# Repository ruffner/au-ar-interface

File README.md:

# au-ar-interface
machine vision and hdmi interface for alchitry labs au artix 7 fpga

## layer stackup
I use pcbway and this is the layer configuration from them that this board is based on. 

## hdmi impedance calcluation and design considerations
Saturn PCB Toolkit was used to calculate the necessary trace widths and spacing to achieve the 100 ohm differential impedance target of the HDMI specification.

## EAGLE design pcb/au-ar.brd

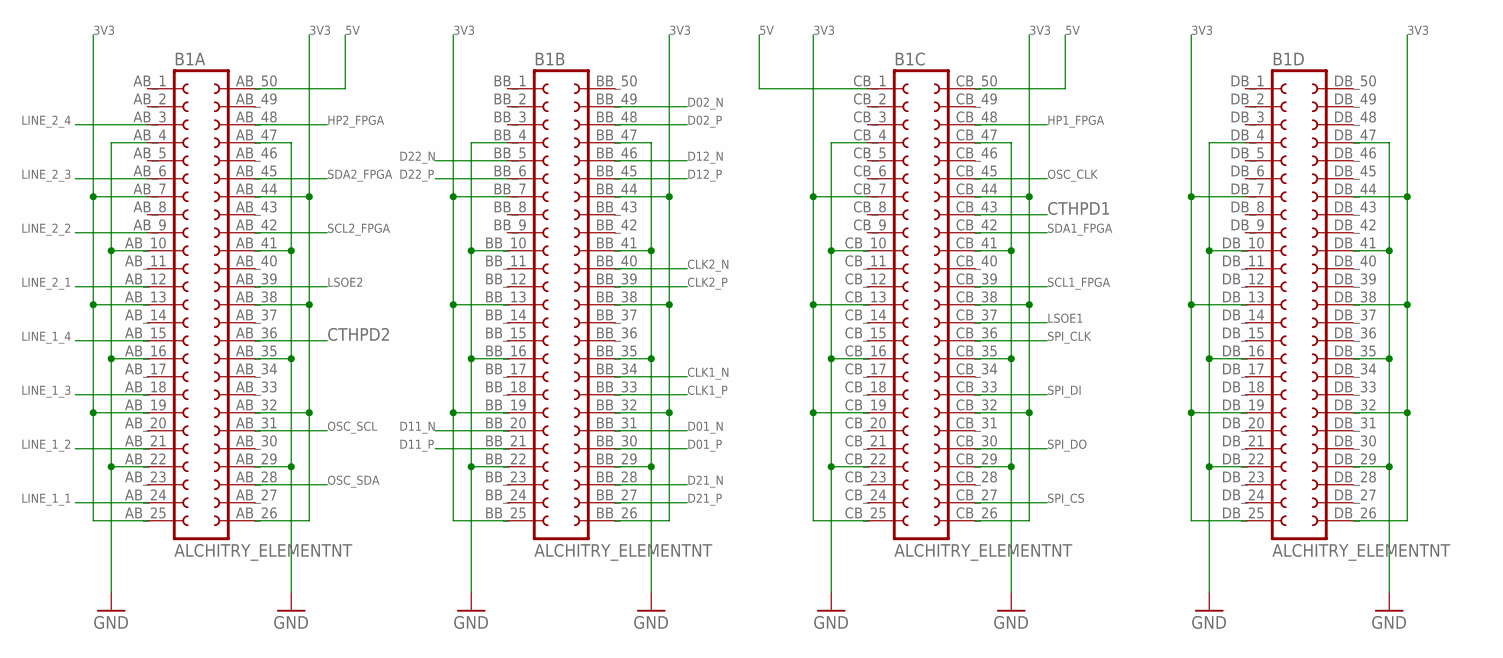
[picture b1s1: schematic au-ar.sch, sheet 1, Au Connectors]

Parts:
B1: ALCHITRY_ELEMENTNT; ELEMENT_NO_TOP

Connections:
3V3: B1.AB_7 (7), B1.AB_13 (13), B1.AB_19 (19), B1.AB_25 (25), B1.AB_26 (26), B1.AB_32 (32), B1.AB_38 (38), B1.AB_44 (44), B1.BB_7 (7), B1.BB_13 (13), B1.BB_19 (19), B1.BB_25 (25), B1.BB_26 (26), B1.BB_32 (32), B1.BB_38 (38), B1.BB_44 (44), B1.CB_7 (7), B1.CB_13 (13), B1.CB_19 (19), B1.CB_25 (25), B1.CB_26 (26), B1.CB_32 (32), B1.CB_38 (38), B1.CB_44 (44), B1.DB_7 (7), B1.DB_13 (13), B1.DB_19 (19), B1.DB_25 (25), B1.DB_26 (26), B1.DB_32 (32), B1.DB_38 (38), B1.DB_44 (44); also elsewhere on the board
5V: B1.AB_50 (50), B1.CB_1 (1), B1.CB_50 (50); also elsewhere on the board
CLK1_N: B1.BB_34 (34); also elsewhere on the board
CLK1_P: B1.BB_33 (33); also elsewhere on the board
CLK2_N: B1.BB_40 (40); also elsewhere on the board
CLK2_P: B1.BB_39 (39); also elsewhere on the board
CTHPD1: B1.CB_43 (43); also elsewhere on the board
CTHPD2: B1.AB_36 (36); also elsewhere on the board
D01_N: B1.BB_31 (31); also elsewhere on the board
D01_P: B1.BB_30 (30); also elsewhere on the board
D02_N: B1.BB_49 (49); also elsewhere on the board
D02_P: B1.BB_48 (48); also elsewhere on the board
D11_N: B1.BB_20 (20); also elsewhere on the board
D11_P: B1.BB_21 (21); also elsewhere on the board
D12_N: B1.BB_46 (46); also elsewhere on the board
D12_P: B1.BB_45 (45); also elsewhere on the board
D21_N: B1.BB_28 (28); also elsewhere on the board
D21_P: B1.BB_27 (27); also elsewhere on the board
D22_N: B1.BB_5 (5); also elsewhere on the board
D22_P: B1.BB_6 (6); also elsewhere on the board
GND: B1.AB_4 (4), B1.AB_10 (10), B1.AB_16 (16), B1.AB_22 (22), B1.AB_29 (29), B1.AB_35 (35), B1.AB_41 (41), B1.AB_47 (47), B1.BB_4 (4), B1.BB_10 (10), B1.BB_16 (16), B1.BB_22 (22), B1.BB_29 (29), B1.BB_35 (35), B1.BB_41 (41), B1.BB_47 (47), B1.CB_4 (4), B1.CB_10 (10), B1.CB_16 (16), B1.CB_22 (22), B1.CB_29 (29), B1.CB_35 (35), B1.CB_41 (41), B1.CB_47 (47), B1.DB_4 (4), B1.DB_10 (10), B1.DB_16 (16), B1.DB_22 (22), B1.DB_29 (29), B1.DB_35 (35), B1.DB_41 (41), B1.DB_47 (47); also elsewhere on the board
HP1_FPGA: B1.CB_48 (48); also elsewhere on the board
HP2_FPGA: B1.AB_48 (48); also elsewhere on the board
LINE_1_1: B1.AB_24 (24); also elsewhere on the board
LINE_1_2: B1.AB_21 (21); also elsewhere on the board
LINE_1_3: B1.AB_18 (18); also elsewhere on the board
LINE_1_4: B1.AB_15 (15); also elsewhere on the board
LINE_2_1: B1.AB_12 (12); also elsewhere on the board
LINE_2_2: B1.AB_9 (9); also elsewhere on the board
LINE_2_3: B1.AB_6 (6); also elsewhere on the board
LINE_2_4: B1.AB_3 (3); also elsewhere on the board
LSOE1: B1.CB_37 (37); also elsewhere on the board
LSOE2: B1.AB_39 (39); also elsewhere on the board
OSC_CLK: B1.CB_45 (45); also elsewhere on the board
OSC_SCL: B1.AB_31 (31); also elsewhere on the board
OSC_SDA: B1.AB_28 (28); also elsewhere on the board
SCL1_FPGA: B1.CB_39 (39); also elsewhere on the board
SCL2_FPGA: B1.AB_42 (42); also elsewhere on the board
SDA1_FPGA: B1.CB_42 (42); also elsewhere on the board
SDA2_FPGA: B1.AB_45 (45); also elsewhere on the board
SPI_CLK: B1.CB_36 (36); also elsewhere on the board
SPI_CS: B1.CB_27 (27); also elsewhere on the board
SPI_DI: B1.CB_33 (33); also elsewhere on the board
SPI_DO: B1.CB_30 (30); also elsewhere on the board

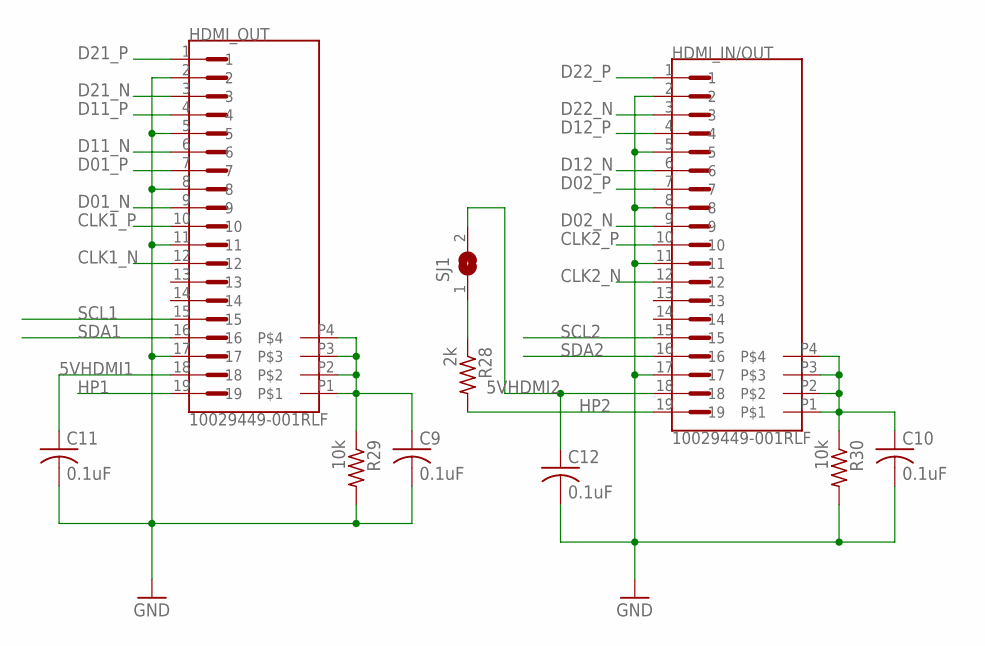
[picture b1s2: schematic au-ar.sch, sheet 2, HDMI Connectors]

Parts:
C9, C10, C11, C12: 0.1uF; C0603
HDMI_IN/OUT: 10029449-001RLF; FCI_10029449-001RLF
HDMI_OUT: 10029449-001RLF; FCI_10029449-001RLF
R28: 2k; R0603
R29, R30: 10k; R0603
SJ1: SJ

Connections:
5VHDMI1: C11.1, HDMI_OUT.18; also elsewhere on the board
5VHDMI2: C12.1, HDMI_IN/OUT.18, SJ1.2; also elsewhere on the board
CLK1_N: HDMI_OUT.12; also elsewhere on the board
CLK1_P: HDMI_OUT.10; also elsewhere on the board
CLK2_N: HDMI_IN/OUT.12; also elsewhere on the board
CLK2_P: HDMI_IN/OUT.10; also elsewhere on the board
D01_N: HDMI_OUT.9; also elsewhere on the board
D01_P: HDMI_OUT.7; also elsewhere on the board
D02_N: HDMI_IN/OUT.9; also elsewhere on the board
D02_P: HDMI_IN/OUT.7; also elsewhere on the board
D11_N: HDMI_OUT.6; also elsewhere on the board
D11_P: HDMI_OUT.4; also elsewhere on the board
D12_N: HDMI_IN/OUT.6; also elsewhere on the board
D12_P: HDMI_IN/OUT.4; also elsewhere on the board
D21_N: HDMI_OUT.3; also elsewhere on the board
D21_P: HDMI_OUT.1; also elsewhere on the board
D22_N: HDMI_IN/OUT.3; also elsewhere on the board
D22_P: HDMI_IN/OUT.1; also elsewhere on the board
GND: C9.2, C10.2, C11.2, C12.2, HDMI_IN/OUT.2, HDMI_IN/OUT.5, HDMI_IN/OUT.8, HDMI_IN/OUT.11, HDMI_IN/OUT.17, HDMI_OUT.2, HDMI_OUT.5, HDMI_OUT.8, HDMI_OUT.11, HDMI_OUT.17, R29.2, R30.2; also elsewhere on the board
HP1: HDMI_OUT.19; also elsewhere on the board
HP2: HDMI_IN/OUT.19, R28.2; also elsewhere on the board
unnamed: R28.1, SJ1.1
unnamed: C9.1, HDMI_OUT.P1, HDMI_OUT.P2, HDMI_OUT.P3, HDMI_OUT.P4, R29.1
unnamed: C10.1, HDMI_IN/OUT.P1, HDMI_IN/OUT.P2, HDMI_IN/OUT.P3, HDMI_IN/OUT.P4, R30.1
SCL1: HDMI_OUT.15; also elsewhere on the board
SCL2: HDMI_IN/OUT.15; also elsewhere on the board
SDA1: HDMI_OUT.16; also elsewhere on the board
SDA2: HDMI_IN/OUT.16; also elsewhere on the board

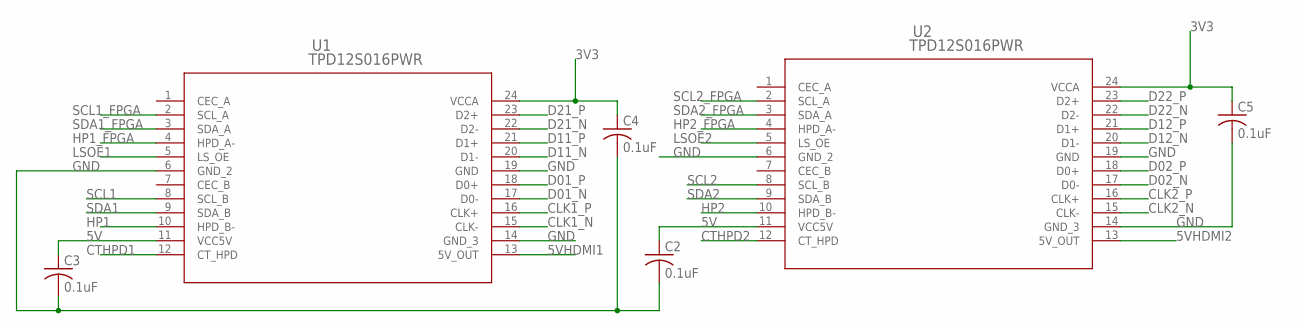
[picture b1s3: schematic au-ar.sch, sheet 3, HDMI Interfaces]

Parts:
C2, C3, C4, C5: 0.1uF; C0603
U1, U2: TPD12S016PWR; PW24

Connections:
3V3: C4.1, C5.1, U1.24 (VCCA), U2.24 (VCCA); also elsewhere on the board
5V: C2.1, C3.1, U1.11 (VCC5V), U2.11 (VCC5V); also elsewhere on the board
5VHDMI1: U1.13 (5V_OUT); also elsewhere on the board
5VHDMI2: U2.13 (5V_OUT); also elsewhere on the board
CLK1_N: U1.15 (CLK-); also elsewhere on the board
CLK1_P: U1.16 (CLK+); also elsewhere on the board
CLK2_N: U2.15 (CLK-); also elsewhere on the board
CLK2_P: U2.16 (CLK+); also elsewhere on the board
CTHPD1: U1.12 (CT_HPD); also elsewhere on the board
CTHPD2: U2.12 (CT_HPD); also elsewhere on the board
D01_N: U1.17 (D0-); also elsewhere on the board
D01_P: U1.18 (D0+); also elsewhere on the board
D02_N: U2.17 (D0-); also elsewhere on the board
D02_P: U2.18 (D0+); also elsewhere on the board
D11_N: U1.20 (D1-); also elsewhere on the board
D11_P: U1.21 (D1+); also elsewhere on the board
D12_N: U2.20 (D1-); also elsewhere on the board
D12_P: U2.21 (D1+); also elsewhere on the board
D21_N: U1.22 (D2-); also elsewhere on the board
D21_P: U1.23 (D2+); also elsewhere on the board
D22_N: U2.22 (D2-); also elsewhere on the board
D22_P: U2.23 (D2+); also elsewhere on the board
GND: C2.2, C3.2, C4.2, C5.2, U1.6 (GND_2), U1.14 (GND_3), U1.19 (GND), U2.6 (GND_2), U2.14 (GND_3), U2.19 (GND); also elsewhere on the board
HP1: U1.10 (HPD_B-); also elsewhere on the board
HP1_FPGA: U1.4 (HPD_A-); also elsewhere on the board
HP2: U2.10 (HPD_B-); also elsewhere on the board
HP2_FPGA: U2.4 (HPD_A-); also elsewhere on the board
LSOE1: U1.5 (LS_OE); also elsewhere on the board
LSOE2: U2.5 (LS_OE); also elsewhere on the board
SCL1: U1.8 (SCL_B); also elsewhere on the board
SCL1_FPGA: U1.2 (SCL_A); also elsewhere on the board
SCL2: U2.8 (SCL_B); also elsewhere on the board
SCL2_FPGA: U2.2 (SCL_A); also elsewhere on the board
SDA1: U1.9 (SDA_B); also elsewhere on the board
SDA1_FPGA: U1.3 (SDA_A); also elsewhere on the board
SDA2: U2.9 (SDA_B); also elsewhere on the board
SDA2_FPGA: U2.3 (SDA_A); also elsewhere on the board

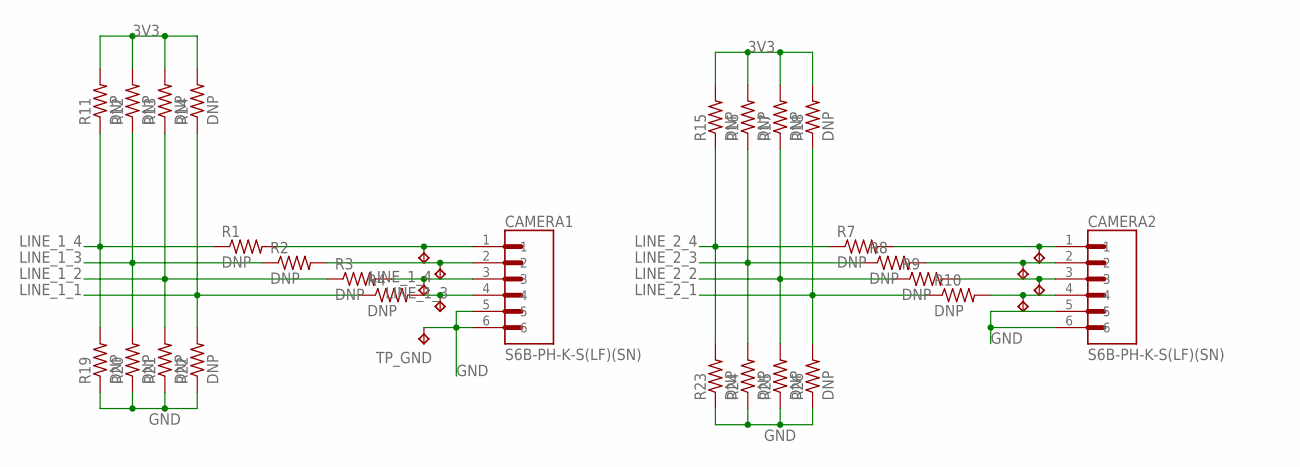
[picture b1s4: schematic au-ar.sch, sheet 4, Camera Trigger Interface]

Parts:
1, 4: LINE_1; TP16R
2: LINE_2; TP16R
3: LINE_3; TP16R
CAMERA1, CAMERA2: S6B-PH-K-S(LF)(SN); JST_S6B-PH-K-S(LF)(SN)
LINE_1_1, LINE_1_2, LINE_1_3, LINE_1_4: TPTP16R; TP16R
R1, R2, R3, R4, R7, R8, R9, R10, R11, R12, R13, R14, R15, R16, R17, R18, R19, R20, R21, R22, R23, R24, R25, R26: DNP; R0603
TP_GND: TPTP16R; TP16R

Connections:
3V3: R11.2, R12.2, R13.2, R14.2, R15.2, R16.2, R17.2, R18.2; also elsewhere on the board
GND: CAMERA1.5, CAMERA1.6, CAMERA2.5, CAMERA2.6, R19.1, R20.1, R21.1, R22.1, R23.1, R24.1, R25.1, R26.1, TP_GND.TP; also elsewhere on the board
LINE_1_1: R4.1, R14.1, R22.2; also elsewhere on the board
LINE_1_2: R3.1, R13.1, R21.2; also elsewhere on the board
LINE_1_3: R2.1, R12.1, R20.2; also elsewhere on the board
LINE_1_4: R1.1, R11.1, R19.2; also elsewhere on the board
LINE_2_1: R10.1, R18.1, R26.2; also elsewhere on the board
LINE_2_2: R9.1, R17.1, R25.2; also elsewhere on the board
LINE_2_3: R8.1, R16.1, R24.2; also elsewhere on the board
LINE_2_4: R7.1, R15.1, R23.2; also elsewhere on the board
unnamed: 4.TP, CAMERA2.1, R7.2
unnamed: 3.TP, CAMERA2.2, R8.2
unnamed: 2.TP, CAMERA2.3, R9.2
unnamed: 1.TP, CAMERA2.4, R10.2
unnamed: CAMERA1.1, LINE_1_4.TP, R1.2
unnamed: CAMERA1.2, LINE_1_3.TP, R2.2
unnamed: CAMERA1.3, LINE_1_2.TP, R3.2
unnamed: CAMERA1.4, LINE_1_1.TP, R4.2

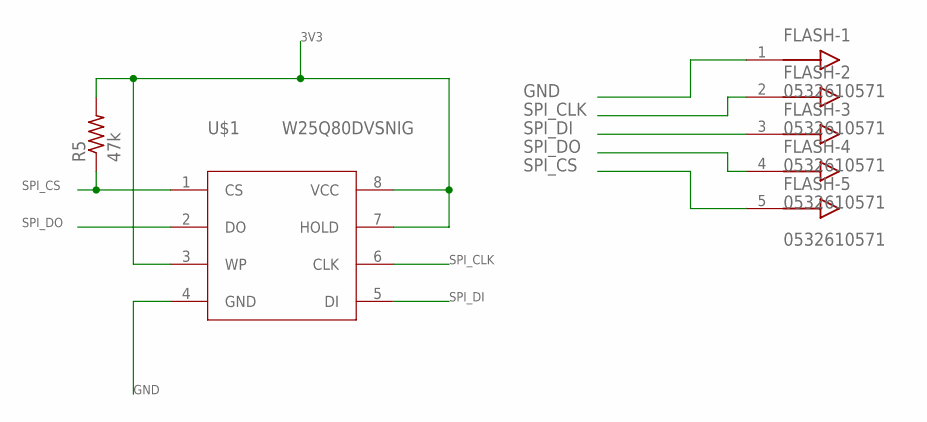
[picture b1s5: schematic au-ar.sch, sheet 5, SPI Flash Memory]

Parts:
FLASH: 0532610571; PICOBLADE53261-0571
R5: 47k; R0603
U$1: W25Q80DVSNIG; SOIC8

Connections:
3V3: R5.2, U$1.3 (WP), U$1.7 (HOLD), U$1.8 (VCC); also elsewhere on the board
GND: FLASH.1, U$1.4 (GND); also elsewhere on the board
SPI_CLK: FLASH.2, U$1.6 (CLK); also elsewhere on the board
SPI_CS: FLASH.5, R5.1, U$1.1 (CS); also elsewhere on the board
SPI_DI: FLASH.3, U$1.5 (DI); also elsewhere on the board
SPI_DO: FLASH.4, U$1.2 (DO); also elsewhere on the board

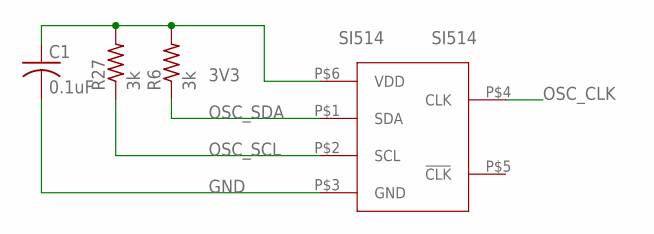
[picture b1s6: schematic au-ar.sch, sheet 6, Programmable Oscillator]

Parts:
C1: 0.1uF; C0603
R6, R27: 3k; R0603
SI514: SI514; XTAL-6PIN

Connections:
3V3: C1.1, R6.2, R27.2, SI514.P$6 (VDD); also elsewhere on the board
GND: C1.2, SI514.P$3 (GND); also elsewhere on the board
OSC_CLK: SI514.P$4 (CLK); also elsewhere on the board
OSC_SCL: R27.1, SI514.P$2 (SCL); also elsewhere on the board
OSC_SDA: R6.1, SI514.P$1 (SDA); also elsewhere on the board

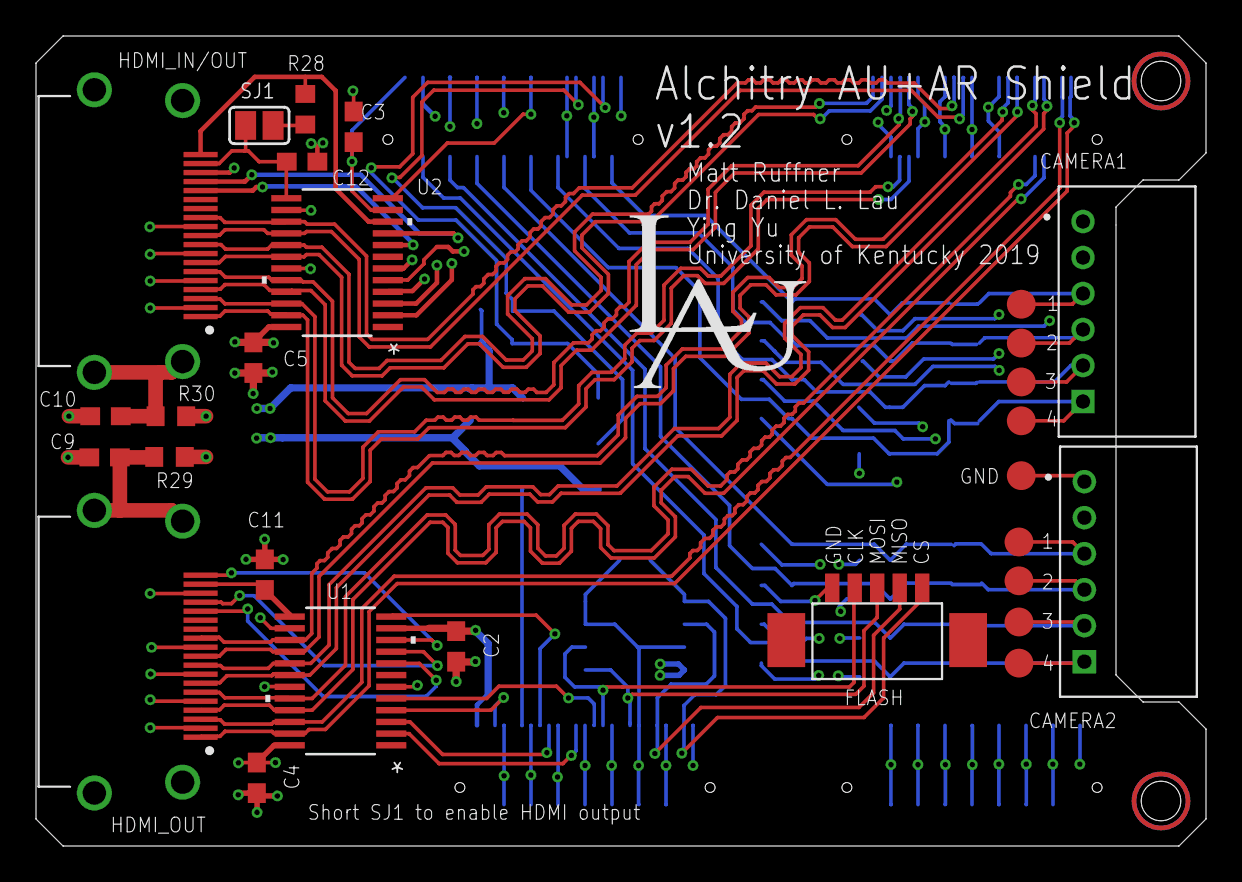
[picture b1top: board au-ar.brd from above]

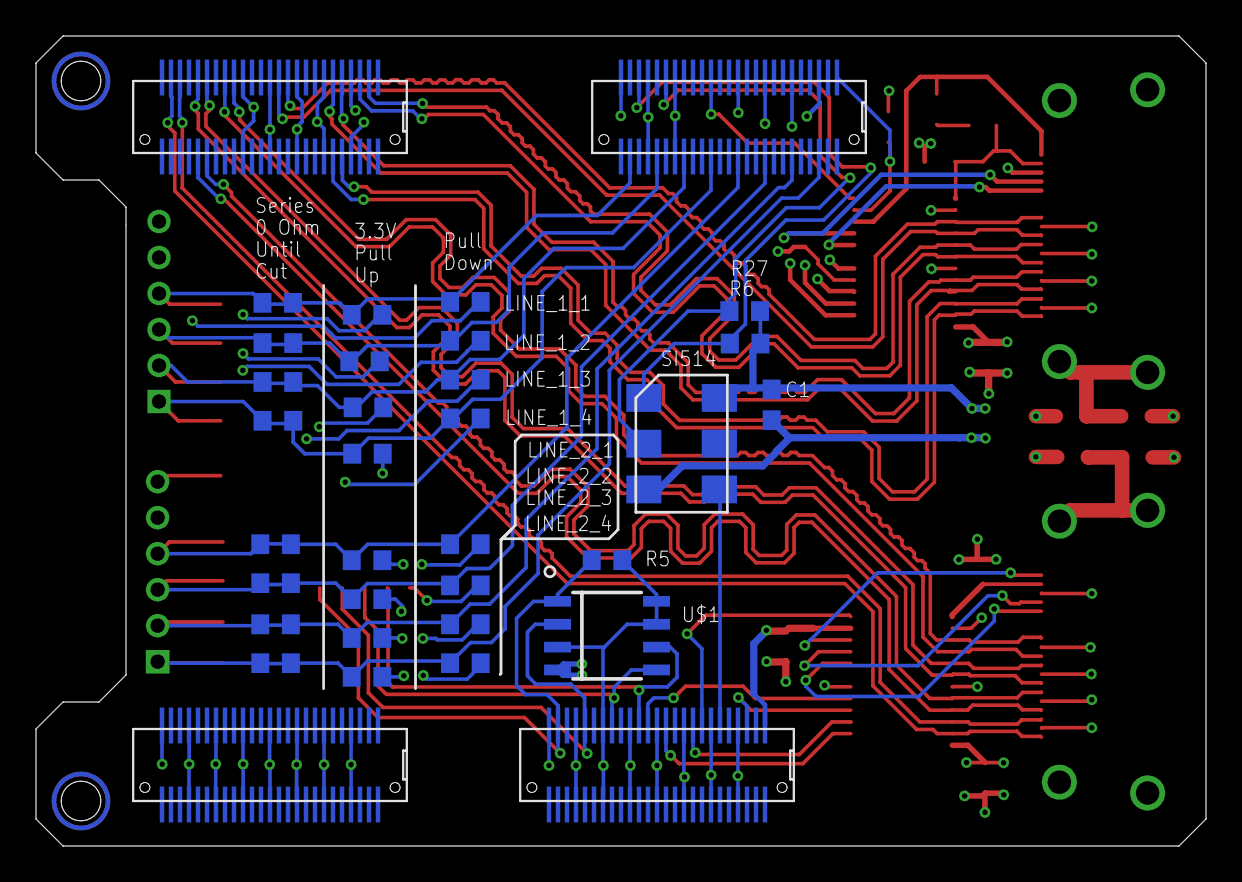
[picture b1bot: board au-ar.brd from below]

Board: 4 copper layers, 65.0 x 45.0 mm, 59 parts (30 on the bottom side), 63 nets.

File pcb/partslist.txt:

Partlist

Exported from au-ar.brd at 8/20/2019 12:37 PM

EAGLE Version 9.4.0 Copyright (c) 1988-2019 Autodesk, Inc.

Assembly variant: 

Part        Value              Package                Library            Position (mil)        Orientation

1           LINE_1             TP16R                  testpad            (2150 665)            R0
2           LINE_2             TP16R                  testpad            (2150 580)            R0
3           LINE_3             TP16R                  testpad            (2150 490)            R0
4           LINE_1             TP16R                  testpad            (2150 400)            R0
B1          ALCHITRY_ELEMENTNT ELEMENT_NO_TOP         alchitry_elements  (0 0)                 R0
C1          0.1uF              C0603                  rcl                (950 965)             MR270
C2          0.1uF              C0603                  rcl                (919 436.5)           R270
C3          0.1uF              C0603                  rcl                (900.5 1364.5)        R270
C4          0.1uF              C0603                  rcl                (483 149)             R270
C5          0.1uF              C0603                  rcl                (475.5 1068)          R270
C9          0.1uF              C0603                  rcl                (150 850)             R180
C10         0.1uF              C0603                  rcl                (152 940)             R180
C11         0.1uF              C0603                  rcl                (500.5 593.5)         R90
C12         0.1uF              C0603                  rcl                (582 1496.75)         R0
CAMERA1     S6B-PH-K-S(LF)(SN) JST_S6B-PH-K-S(LF)(SN) S6B-PH-K-S_LF__SN_ (2290 1169)           R90
CAMERA2     S6B-PH-K-S(LF)(SN) JST_S6B-PH-K-S(LF)(SN) S6B-PH-K-S_LF__SN_ (2293 600)            R90
FLASH       0532610571         PICOBLADE53261-0571    volks73-Molex      (1836 470)            R0
HDMI_IN/OUT 10029449-001RLF    FCI_10029449-001RLF    10029449-001RLF    (360 1345)            R270
HDMI_OUTPUT 10029449-001RLF    FCI_10029449-001RLF    10029449-001RLF    (360 425)             R270
LINE_1_1    TPTP16R            TP16R                  testpad            (2155 1185)           R0
LINE_1_2    TPTP16R            TP16R                  testpad            (2155 1100)           R0
LINE_1_3    TPTP16R            TP16R                  testpad            (2155 1015)           R0
LINE_1_4    TPTP16R            TP16R                  testpad            (2155 930)            R0
R1          DNP                R0603                  rcl                (2030 930)            MR180
R2          DNP                R0603                  rcl                (2030 1015)           MR180
R3          DNP                R0603                  rcl                (2030 1100)           MR180
R4          DNP                R0603                  rcl                (2030 1185)           MR180
R5          47k                R0603                  rcl                (1310 625)            MR0
R6          3k                 R0603                  rcl                (1008 1099)           MR0
R7          DNP                R0603                  rcl                (2035 400)            MR180
R8          DNP                R0603                  rcl                (2035 485)            MR180
R9          DNP                R0603                  rcl                (2035 575)            MR180
R10         DNP                R0603                  rcl                (2035 660)            MR180
R11         DNP                R0603                  rcl                (1834 858)            MR0
R12         DNP                R0603                  rcl                (1837 955)            MR0
R13         DNP                R0603                  rcl                (1836 1051)           MR0
R14         DNP                R0603                  rcl                (1835 1155)           MR0
R15         DNP                R0603                  rcl                (1835 370)            MR0
R16         DNP                R0603                  rcl                (1835 455)            MR0
R17         DNP                R0603                  rcl                (1835 540)            MR0
R18         DNP                R0603                  rcl                (1835 625)            MR0
R19         DNP                R0603                  rcl                (1620 935)            MR180
R20         DNP                R0603                  rcl                (1620 1020)           MR180
R21         DNP                R0603                  rcl                (1620 1105)           MR180
R22         DNP                R0603                  rcl                (1620 1190)           MR180
R23         DNP                R0603                  rcl                (1620 400)            MR180
R24         DNP                R0603                  rcl                (1620 485)            MR180
R25         DNP                R0603                  rcl                (1620 570)            MR180
R26         DNP                R0603                  rcl                (1620 660)            MR180
R27         3k                 R0603                  rcl                (1009 1170)           MR0
R28         2k                 R0603                  rcl                (589 1607.75)         R90
R29         10k                R0603                  rcl                (292 851)             R0
R30         10k                R0603                  rcl                (295 940)             R0
SI514       SI514              XTAL-6PIN              lupa300-components (1147 880)            MR0
SJ1                            SJ                     jumper             (488.5 1576)          R180
TP_GND      TPTP16R            TP16R                  testpad            (2155 810)            R0
U$1         W25Q80DVSNIG       SOIC8                  TDP12S521          (1310 460)            MR270
U1          TPD12S016PWR       PW24                   lupa300-components (666 361)             R180
U2          TPD12S016PWR       PW24                   lupa300-components (658.5 1276)          R180

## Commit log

2019-04-10 started au-ar layout
2019-04-10 added .gitignore
2019-04-11 placed signal config resistors for camera trigger interface. relocated hdmi ports
2019-04-12 rearranged hdmi ports. removed end mounting holes to make room for dual ports on the end. added footprint for spi flash and added to schematic.
2019-04-15 added remaining connections in schematic for spi flash and hdmi ddc bus
2019-04-15 started routing hdmi tmds signals. had to make min hole size .2mm
2019-04-15 more routing
2019-04-18 reorganized hdmi pins, hdmi routing almost done
2019-04-22 routed hdmi, need to route low speed signals
2019-04-24 added more routing
2019-04-29 added final edits for v1 order and pcbway gerbers
2019-05-10 added external oscillator
2019-05-31 started rerouting with new esd protection chips
2019-05-31 almost done routing
2019-06-04 need to add mosfet and order
2019-07-05 added most recent gerbers
2019-07-05 updated newest gerbers
2019-08-20 retuned hdmi trace lengths, added ground pour and cutouts under hdmi connectors
2019-08-20 added partslist and solder jumper for hdmi input, labeled hdmi input and output added up to date gerbers.
2019-08-28 added version from school pc
2019-08-28 add gerbers from hpd-mosfet fab run
2019-09-30 hdmi ground vias moved
2019-09-30 v1.2 silk edits
2019-09-30 final mods to v1.2 pcb and addition of v1.2 gerbers
2019-09-30 remove old partslist, add v1.2 partslist
2019-09-30 add images of layer stackup and imped. calc.

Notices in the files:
parts and their libraries:
volks73-Molex: Creative Commons Attribution-ShareAlike 3.0 Unported (CC BY-SA 3.0), http://creativecommons.org/licenses/by-sa/3.0/.
